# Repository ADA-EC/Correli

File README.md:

# Projeto Correli
Projeto desenvolvido pelo Grupo ADA - Projetos em Engenharia de Computação em parceiria com o Departamento de Estruturas da EESC - USP.

## Configuração
É necessário que um Arduino esteja conectado a uma porta USB do computador para que o código seja executado corretamente.

### Ubuntu
Antes de executar o código no sistesma operacional Ubuntu (os testes foram realizados no Ubuntu 18.04), é necessário possuir o [Python versão 3](https://www.python.org/download/releases/3.0/), e instalar as seguintes bibliotecas:

- [tkinter](https://docs.python.org/3/library/tkinter.html)
- [pyserial](https://pyserial.readthedocs.io/en/latest/pyserial.html) 
- [serial.tools.list_ports](https://pyserial.readthedocs.io/en/latest/tools.html)

Para rodar o código, digitar o seguinte comando no terminal:
   
   `$ python3 interface.py`
 
### Windows
No WIndows, basta rodar o executável previamente criado com Pyinstaller que o programa será executado normalmente. Para executar o código a partir do aquivo Python, é necessário possuir as mesmas bibliotecas e versão do Python exigida para execução em Linux e clicar duas vezes no programa para executá-lo.

## Descrição do Projeto
Criação de um sistema que integre uma prensa hidráulica e uma câmera que tira fotos do corpo de prova que é submetido ao ensaio na prensa. Por meio de uma interface gráfica, o usuário escolhe o modo de operação da camêra (por tempo ou por intervalo de força realizado pela prensa) para tirar a foto. Os dados do ensaio e as tensões nos momentos em que as fotos s
ão tiradas são registrados em um arquivo que fica salvo no final da execução. 

### Prensa Hidráulica
A prensa possui uma saída de tensão que pode ser relacionada com a força que está sendo aplicada em um corpo de prova. Essa tensão pode variar entre -10 volts e 10 volts, a princípio iremos considerar apenas os valores positivos (0-10 volts), tendo uma precisão de 4 casas decimais na leitura dessa tensão e, por fim, podemos convertê-la para força, uma vez que a cada volt temos 25 toneladas sendo aplicado. 

### Câmera
Já a câmera (Canon EOS 30D), possui um função de acionamento remoto, com isso, podemos tirar uma foto sem necessariamente pressionarmos o botão. A ideia do projeto é integrar as fotos tiradas com a força que está sendo aplicada naquele momento e criar um arquivo “.txt”  contendo essa informações. O acionamento da câmera pode ser regulado tanto pelo tempo, tirando fotos em certos intervalos de tempo, quanto por certo intervalos de forças.

### Interface Gráfica
A interface gráfica foi feita em Python. Ela permite que o usuário crie um arquivo com o nome escolhido por ele, escolha a forma de acionamento da câmera (por tempo ou pressão) e defina o intervalo que seja mais conveniente a ele. Então é iniciado o programa, ele se conecta com o código criado para o Arduino Nano e, então, aparece na tela os valores obtidos da pressão que a prensa hidráulica exerce no exato momento em que a foto é tirada. Para utiliza-lá é preciso que o usuário possua tanto o [Python](https://www.python.org/download/releases/3.0/) quanto a biblioteca [PySerial](https://github.com/pyserial/pyserial) instaladas. 

### Prototipagens
O esquemático apresenta o circuito com Arduino, Relé e conversor AD de maneira que seja possível o acionamento da câmera em intervalos especificados pelo usuário de tempo ou tensão.
Simulou-se a prensa para que fosse possível realizar alguns testes. Para isso, utilizou-se 2 potenciômetros conectados, em que um limita a tensão recebida pela fonte (que é de 12V) em até 10V e o segundo simula as tensões que seriam enviadas pela prensa hidráulica.
A câmera é conectada nos terminais do relé indicados no esquemático. Ela tira fotos quando o circuito é fechado pelo relé, em intervalos de tempo ou tensão definidos pelo código.

No segundo modelo feito, utilizou-se um Arduino Nano ao invés do Uno. Também não foi necessário utilizar 2 potenciômetros para simular a prensa, apenas 1. Abaixo está o esquemático do segundo modelo.

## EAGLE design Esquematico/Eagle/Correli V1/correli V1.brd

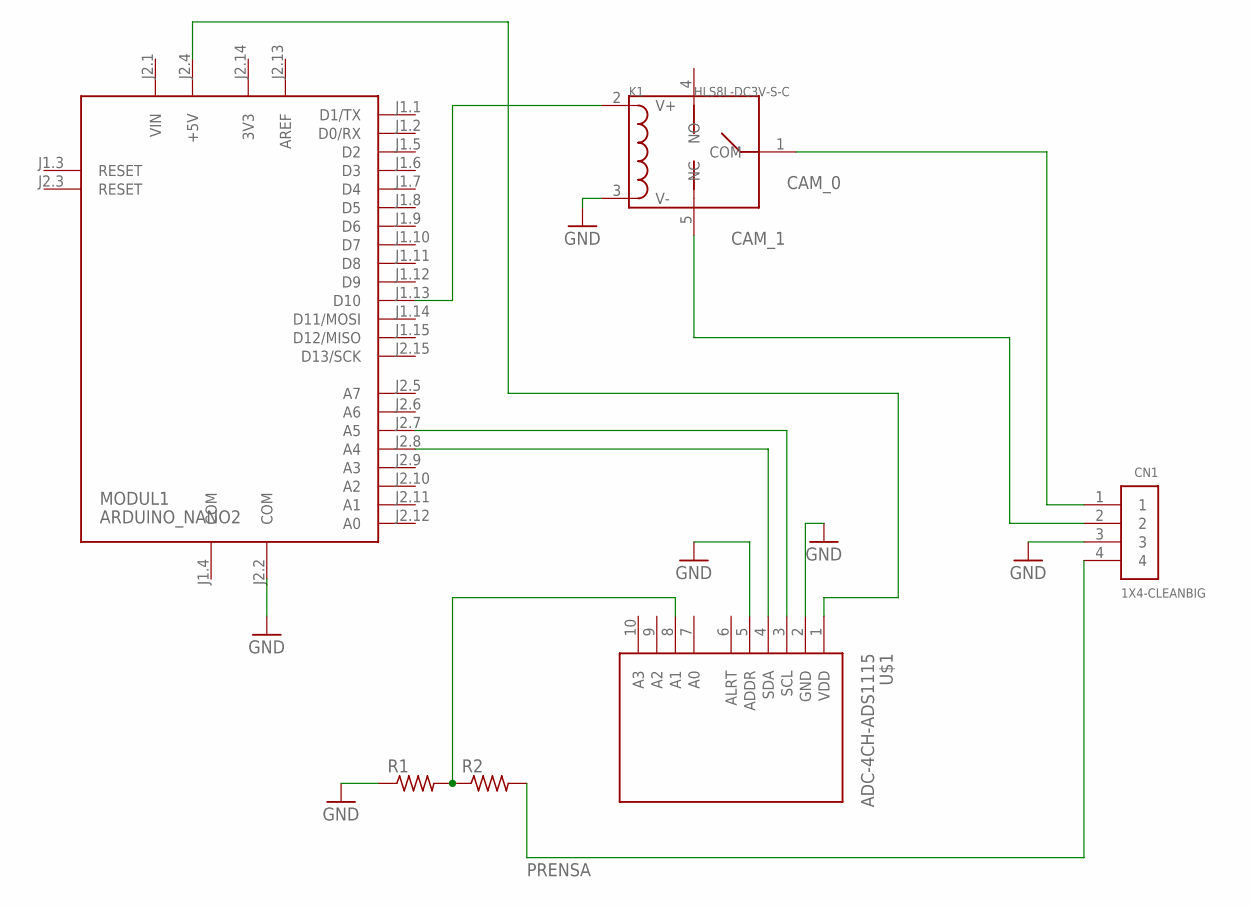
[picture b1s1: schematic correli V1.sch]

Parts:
CN1: 1X4-CLEANBIG; 1X04-CLEANBIG
K1: HLS8L-DC3V-S-C; REY5-19.0X15.0X15.0MM
MODUL1: ARDUINO_NANO2
R1, R2: R-US_0309/12; 0309/12
U$1: ADC-4CH-ADS1115

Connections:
3V3: MODUL1.J2.14 (3V3)
AREF: MODUL1.J2.13 (AREF)
CAM_0: CN1.1, K1.1 (COM)
CAM_1: CN1.2, K1.5 (NC)
COM: MODUL1.J1.4 (COM)
GND: CN1.3, K1.3 (V-), MODUL1.J2.2 (COM), R1.1, U$1.2 (GND), U$1.5 (ADDR)
unnamed: K1.2 (V+), MODUL1.J1.13 (D10)
unnamed: MODUL1.J2.4 (+5V), U$1.1 (VDD)
unnamed: MODUL1.J2.7 (A5), U$1.3 (SCL)
unnamed: MODUL1.J2.8 (A4), U$1.4 (SDA)
unnamed: R1.2, R2.1, U$1.8 (A1)
PRENSA: CN1.4, R2.2
VIN: MODUL1.J2.1 (VIN)

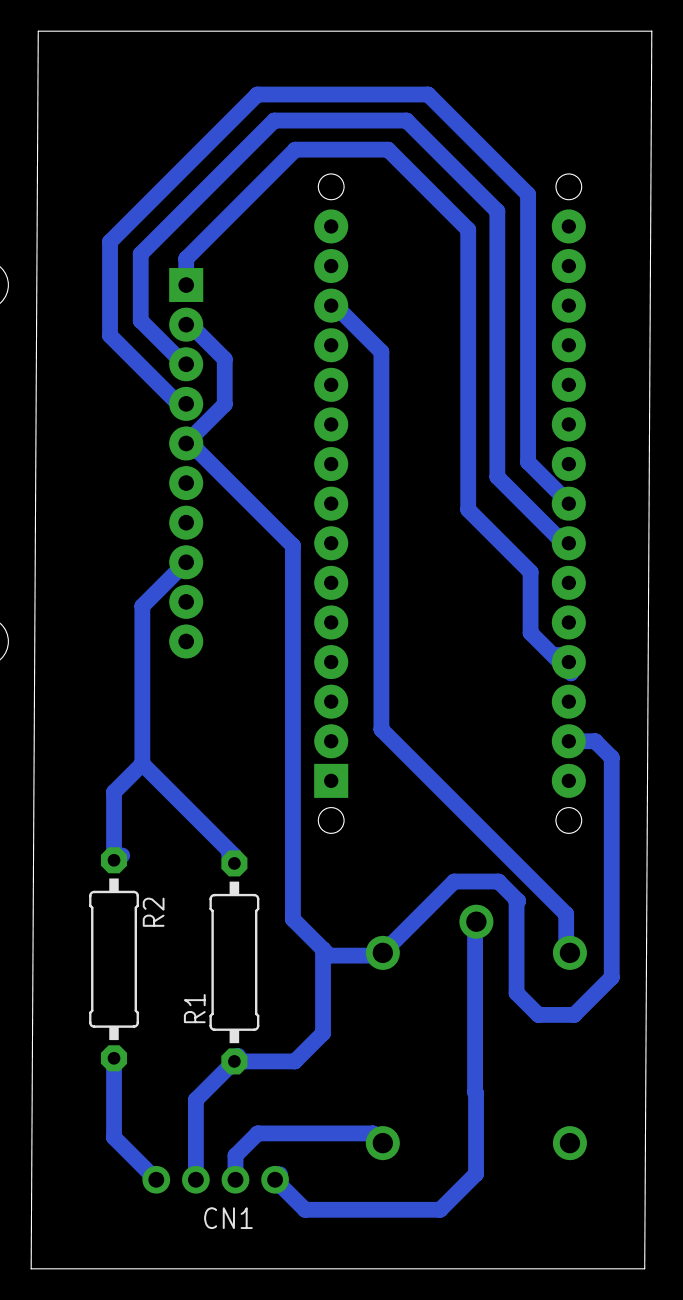
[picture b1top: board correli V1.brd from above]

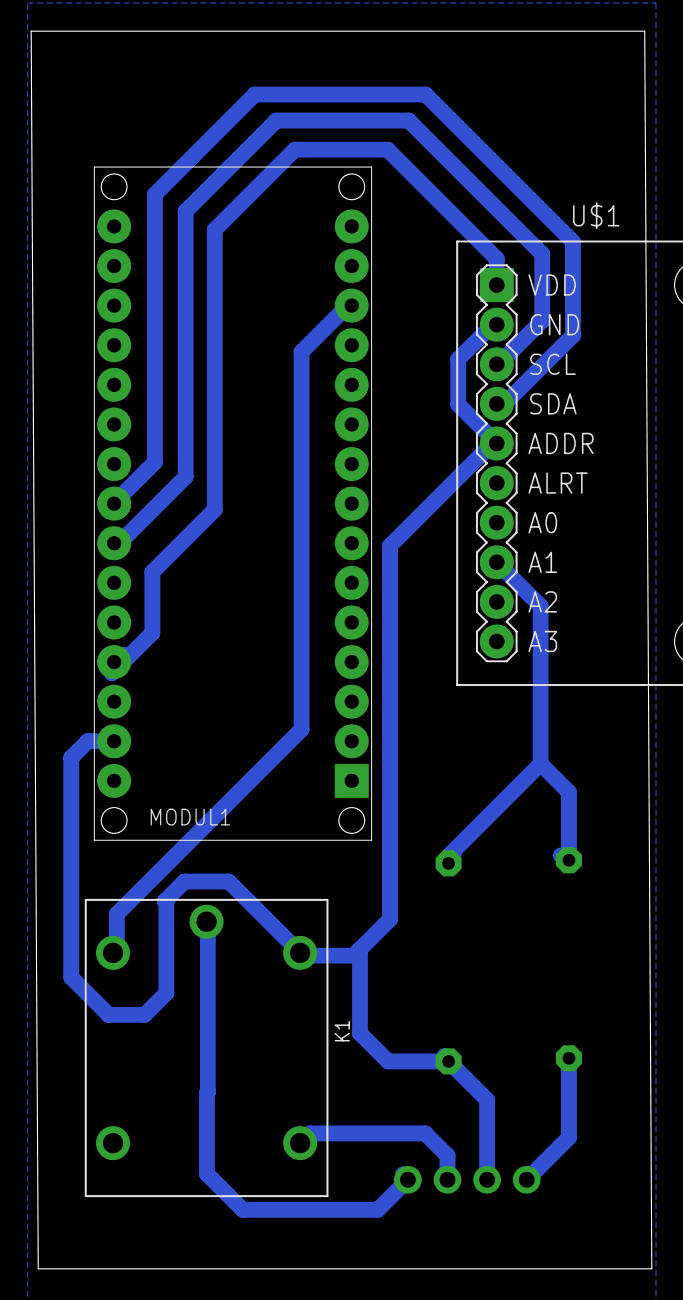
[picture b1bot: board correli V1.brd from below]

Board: 2 copper layers, 39.8 x 79.4 mm, 6 parts (3 on the bottom side), 9 nets.

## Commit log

2019-05-21 Descrição dos modulos a serem utilziados
2019-05-27 Código e circuito do conversor AD adicionado
2019-05-29 Código teste relé com conversor
2019-05-29 Código teste de acionamento do rele por tempo
2019-05-30 foto adicionada
2019-05-30 Atualização no código de acionamento por tempo
2019-05-30 apaguei uma imagem
2019-05-30 Criei essa pasta para ficar mais fácil de entrar no código do Arduino
2019-06-04 Codigo unido atualizado
2019-06-04 Pasta que contem o codigo unido de medicao por tempo e por tensao
2019-06-04 pasta com o esquemático do circuito montado
2019-06-04 README atualizado
2019-06-04 Imagem em png do esquemático montado pela Ada
2019-06-07 Pasta com a interface gráfica ainda não terminada em Python
2019-06-07 README com um breve resumo do funcionamento da interface gráfica adicionado a ele
2019-06-07 Arrumei um erro no nome de uma das variáveis
2019-07-01 Agora a interface printa os valores obtidos pelo Arduino da prensa
2019-07-04 Implementacao da comunicacao serial por meio da linguagem Python
2019-08-12 Interface com fundo de escala
2019-08-12 código de integraão adicionado
2019-08-19 Integracao do codigo da interface grafica com comunicacao serial
2019-08-27 Interface com botão de reiniciar e fechar programa
2019-09-09 Arduino recebe configuracoes
2019-09-09 Interface gráfica com conexão entre ela e o Arduino
2019-09-16 Interface arrumada
2019-09-16 código do sistema atualizado
2019-09-16 Correção de bugs
2019-09-20 Autoscroll implementado, arquivo agora armazena os valores e botão fechar funcional com arduino
2019-09-30 Interface com botão de fechar sem bug
2019-10-01 Readme atualizado com novo esquemático
2019-10-01 Esquemáticos do Arduino Nano adicionados
2019-10-07 Iniciando a criaçao do instalador da interface
2019-11-28 Interface FInalizada
2019-11-28 Esquematico da placa em Eagle
2019-11-29 Executável do código inserido
2019-12-22 Arquivos de teste excluídos
2020-01-06 Dois arquivos da pasta Codigo_Sistema foram deletados por nao mais serem uteis para o projeto
2020-01-16 Interface gráfica comentada
2020-02-04 Codigo_Sistema com novos comentarios
2020-03-23 Adicionei um programa que fiz para aprender a mexer com arquivos .json
2020-03-23 Comentários
2020-03-24 Interface arrumada com janela para início de ensaio
2020-03-24 Interface com opção de local de salvamento do arquivo
2020-03-30 Interface com opção de escolha entre Arduinos e em uma única página
2020-03-30 Interface com opção de escolha entre Arduinos, em uma única página e só permitindo inserir números
2020-04-06 Interface com somente 1 página
2020-04-08 2 tipos de interface, uma com somente 1 página de configurações e a original
2020-04-08 2 tipos de interface, uma com somente 1 página de configurações e outra original
2020-04-11 Interface com aparência mudada
2020-04-11 Codigo ADC atualizado
2020-04-12 Interface única com algumas funções arrumadas
2020-04-14 Interface sem bugs e perfeita!
2020-04-15 Interface sem bugs e comentada!
2020-08-17 Criacao das funcoes que salvam e carregam configuracoes json
2020-08-17 Havia esquecido de adicionar um biblioteca
2020-09-03 Finalizacao da interface grafica
2020-10-26 Bugs arrumados e usuário não pode inserir parametro vazio
2020-11-25 Criacao do executavel da interface de pagina unica
2020-11-25 Corrigindo erro do ultimo commit
2020-11-27 Update executavel
2020-11-27 Interface sem os prints
2020-11-27 Update executavel interface
2020-11-27 Executável add na pasta de executáveis
2021-03-15 Documentos para impressão 3D da caixa adicionados

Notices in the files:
parts and their libraries:
diy-modules: Released under the Creative Commons Attribution 4.0 International License: http://creativecommons.org/licenses/by/4.0
